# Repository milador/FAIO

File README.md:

# FAIO - Feather All-in-One Switch Wings

FAIO assistive technology wings are assistive technology wings developed to provide a modular solution for those with high level of physical disabilities to interact with touch screen devices and personal computers.

## FAIO 1.0

Faio 1.0 is no longer under development and deprecated in favor of new FAIO 2.0 feather assistive technology wings.

## FAIO 2.0

Faio 2.0 is available in two different versions:

1. <a href="https://github.com/milador/FAIO-Multiplexer">FAIO-Multiplexer</a>
2. <a href="https://github.com/milador/FAIO-Sip-And-Puff">FAIO-Sip-And-Puff</a>

## License 

### MIT License

Copyright (c) 2017 Milador

Permission is hereby granted, free of charge, to any person obtaining a copy of this software and associated documentation files (the "Software"), to deal in the Software without restriction, including without limitation the rights to use, copy, modify, merge, publish, distribute, sublicense, and/or sell copies of the Software, and to permit persons to whom the Software is furnished to do so, subject to the following conditions:

The above copyright notice and this permission notice shall be included in all copies or substantial portions of the Software.

THE SOFTWARE IS PROVIDED "AS IS", WITHOUT WARRANTY OF ANY KIND, EXPRESS OR IMPLIED, INCLUDING BUT NOT LIMITED TO THE WARRANTIES OF MERCHANTABILITY, FITNESS FOR A PARTICULAR PURPOSE AND NONINFRINGEMENT. IN NO EVENT SHALL THE AUTHORS OR COPYRIGHT HOLDERS BE LIABLE FOR ANY CLAIM, DAMAGES OR OTHER LIABILITY, WHETHER IN AN ACTION OF CONTRACT, TORT OR OTHERWISE, ARISING FROM, OUT OF OR IN CONNECTION WITH THE SOFTWARE OR THE USE OR OTHER DEALINGS IN THE SOFTWARE.

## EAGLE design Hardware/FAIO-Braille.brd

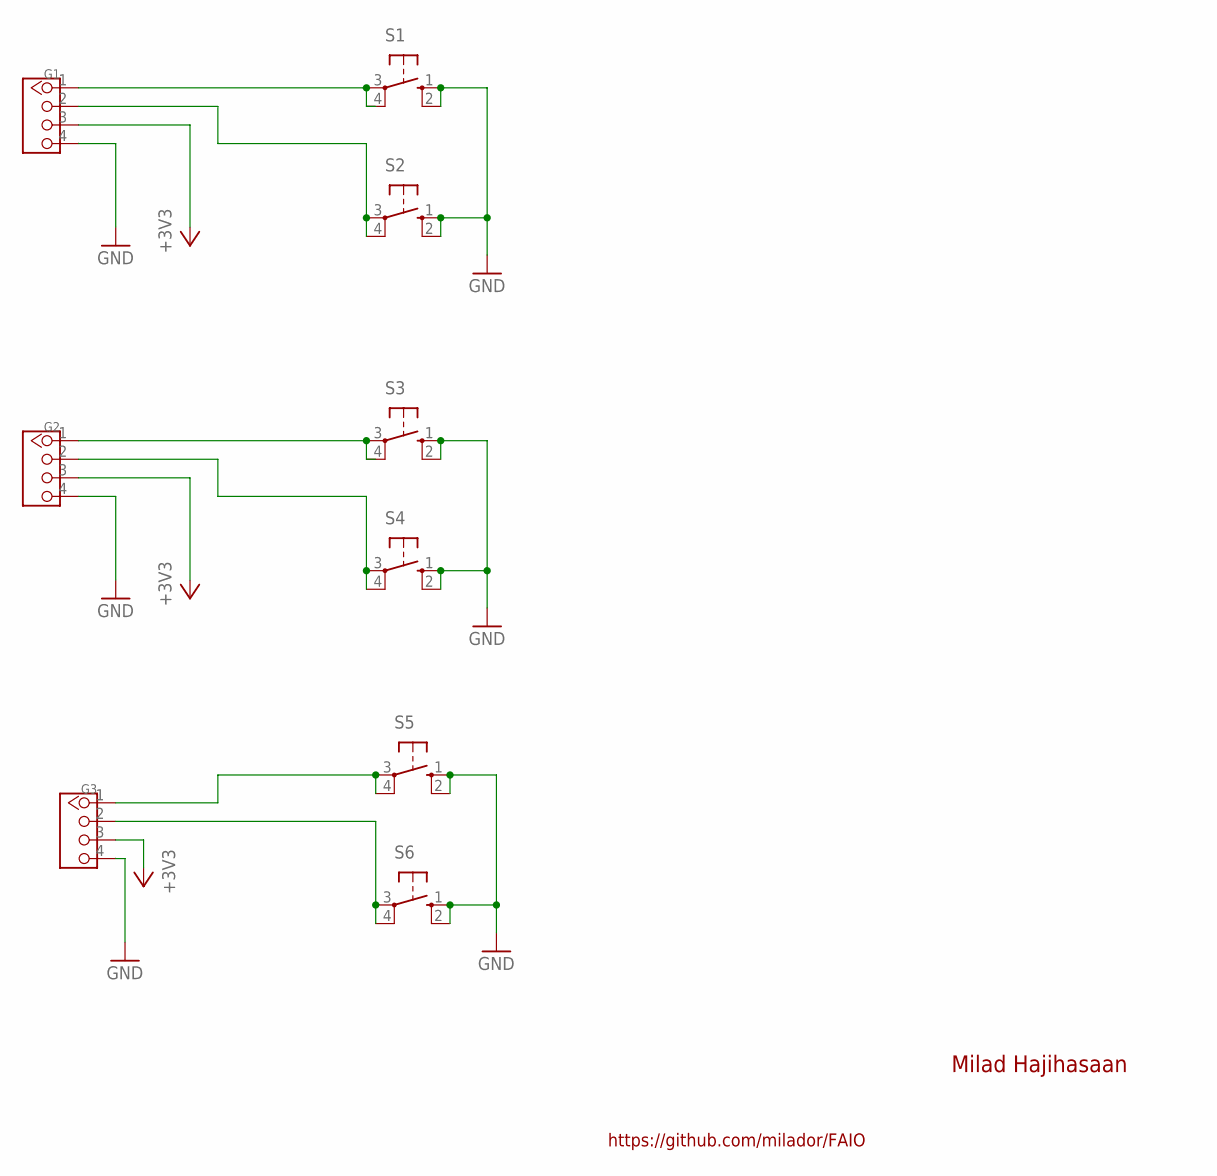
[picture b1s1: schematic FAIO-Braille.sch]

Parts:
G1, G2, G3: TWIG-4P-2.0'90D'; 4P-2.0-90D
S1, S2, S3, S4, S5, S6: 10-XX; B3F-10XX

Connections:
+3V3: G1.3, G2.3, G3.3
GND: G1.4, G2.4, G3.4, S1.1 (S), S1.2 (S1), S2.1 (S), S2.2 (S1), S3.1 (S), S3.2 (S1), S4.1 (S), S4.2 (S1), S5.1 (S), S5.2 (S1), S6.1 (S), S6.2 (S1)
unnamed: G1.1, S1.3, S1.4 (P1)
unnamed: G1.2, S2.3, S2.4 (P1)
unnamed: G2.1, S3.3, S3.4 (P1)
unnamed: G2.2, S4.3, S4.4 (P1)
unnamed: G3.2, S6.3, S6.4 (P1)
unnamed: G3.1, S5.3, S5.4 (P1)

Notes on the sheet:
Milad Hajihasaan
https://github.com/milador/FAIO

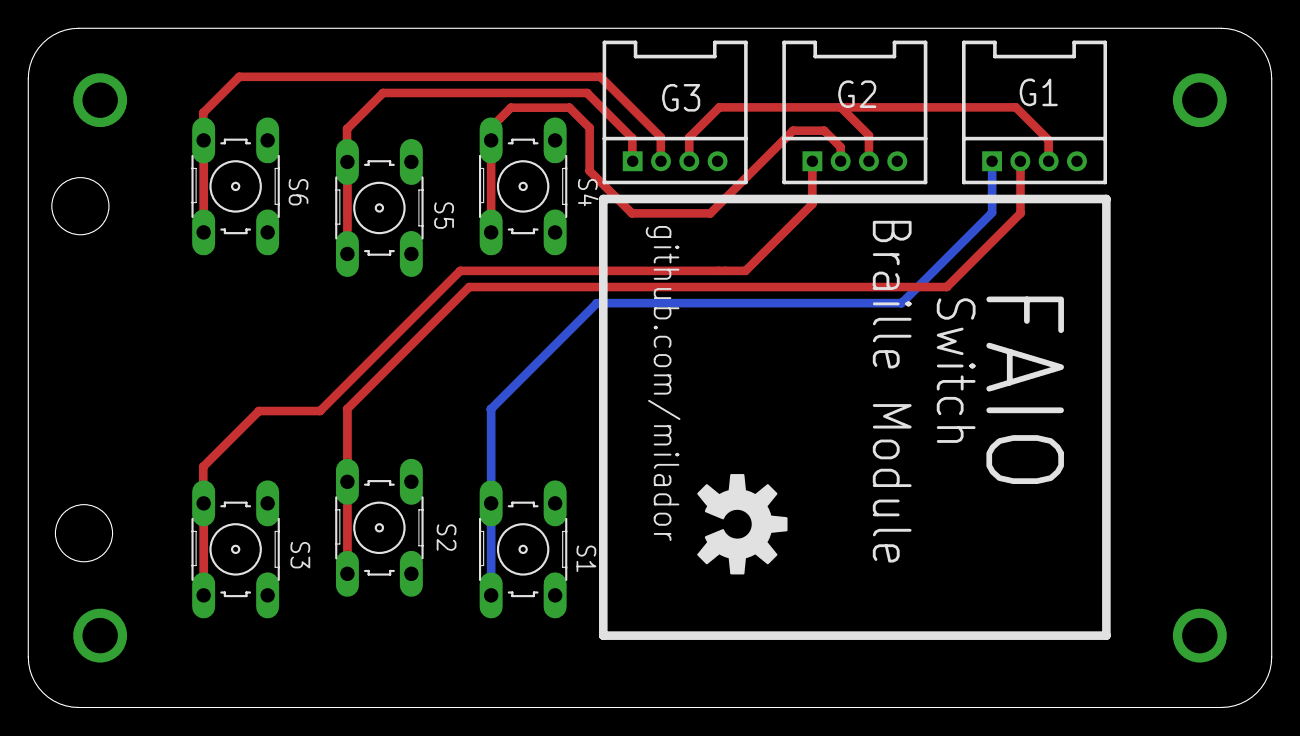
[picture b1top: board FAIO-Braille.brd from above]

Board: 2 copper layers, 87.9 x 48.0 mm, 10 parts (0 on the bottom side), 8 nets.

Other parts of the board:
U$1: OSHW-LOGO-L

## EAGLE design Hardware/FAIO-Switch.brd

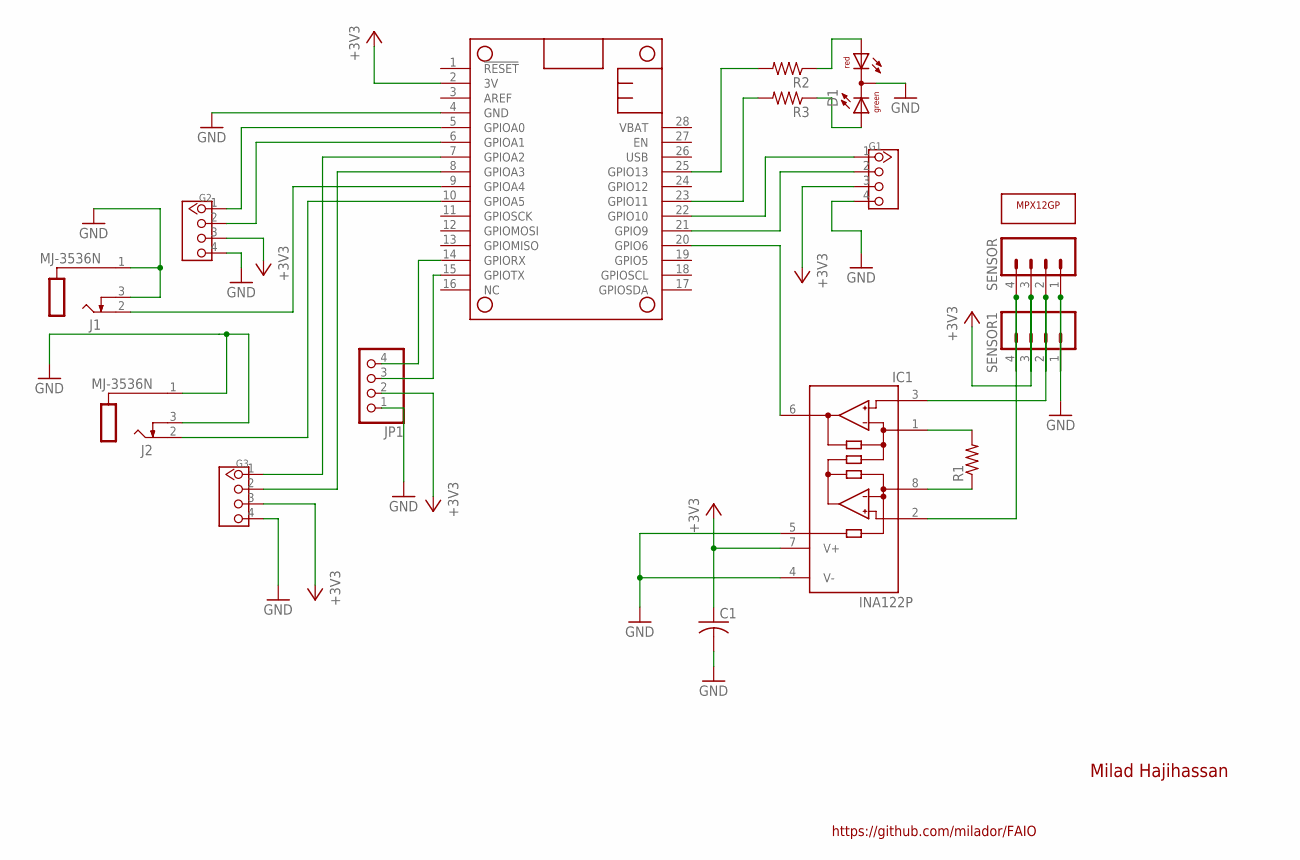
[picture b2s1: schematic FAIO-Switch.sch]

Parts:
C1: C-US025-024X044; C025-024X044
D1: DUOLED5MM
G1, G2, G3: TWIG-4P-2.0'90D'; 4P-2.0-90D
IC1: INA122P; DIL08
J1, J2: MJ-3536N
JP1: PINHD-1X4; 1X04
MS1: FEATHERWING_NODIM; FEATHERWING_DIM
R1, R2, R3: R-US_0204/7; 0204/7
SENSOR, SENSOR1: M04PTH; 1X04
U1: MPX12GP

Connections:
+3V3: C1.1, G1.3, G2.3, G3.3, IC1.7 (V+), JP1.2, MS1.2 (3V), SENSOR.3, SENSOR1.3
GND: C1.2, D1.K (C), G1.4, G2.4, G3.4, IC1.4 (V-), IC1.5 (REF), J1.1 (S), J1.3 (TS), J2.1 (S), J2.3 (TS), JP1.1, MS1.4 (GND), SENSOR.1, SENSOR1.1
unnamed: IC1.3 (+IN), SENSOR.2, SENSOR1.2
unnamed: IC1.2 (-IN), SENSOR.4, SENSOR1.4
unnamed: IC1.1 (RG), R1.2
unnamed: IC1.8 (RG), R1.1
unnamed: MS1.25 (GPIO13), R2.2
unnamed: D1.AR, R2.1
unnamed: D1.AG, R3.1
unnamed: MS1.23 (GPIO11), R3.2
unnamed: IC1.6 (OUT), MS1.20 (GPIO6)
unnamed: JP1.3, MS1.15 (GPIOTX)
unnamed: J1.2 (T), MS1.9 (GPIOA4)
unnamed: JP1.4, MS1.14 (GPIORX)
unnamed: G3.1, MS1.7 (GPIOA2)
unnamed: G1.1, MS1.22 (GPIO10)
unnamed: J2.2 (T), MS1.10 (GPIOA5)
unnamed: G2.2, MS1.6 (GPIOA1)
unnamed: G2.1, MS1.5 (GPIOA0)
unnamed: G1.2, MS1.21 (GPIO9)
unnamed: G3.2, MS1.8 (GPIOA3)

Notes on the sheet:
https://github.com/milador/FAIO
Milad Hajihassan

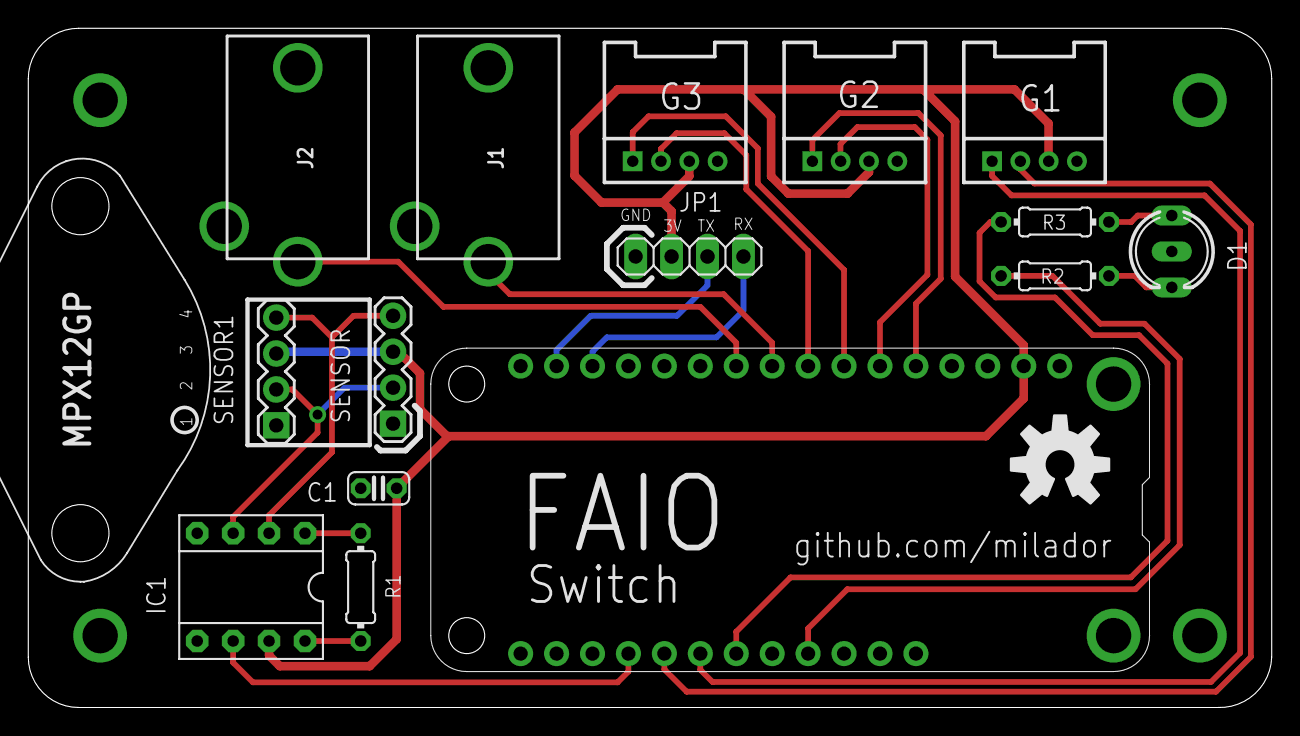
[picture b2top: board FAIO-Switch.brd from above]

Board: 2 copper layers, 87.9 x 48.0 mm, 17 parts (0 on the bottom side), 21 nets.

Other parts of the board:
U$1: OSHW-LOGO-L

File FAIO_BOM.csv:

Index,Version ,Quantity,Part Number,Manufacturer Part Number,Description,Customer Reference,Backorder,Unit Price (CAD),Total Price (CAD)
1,All,1,1597-1083-ND,110990037,GROVE 2MM 4PIN R/A CONN 10PACK,,0,2.05,
2,All,1,INA122PA-ND,INA122PA,IC OPAMP INSTR 120KHZ 8DIP,,0,8.63,
3,All,1,S5479-ND,PPPC041LGBN-RC,"CONN FEMALE 4POS .100"" R/A GOLD",,0,1.02,
4,All,2,CP-3536N-ND,MJ-3536N,CONN JACK MONO 3.5MM R/A,,0,0.94,
5,All,1,S7045-ND,PPPC121LFBN-RC,"CONN HEADER FMALE 12POS .1"" GOLD",,0,1.36,
6,All,1,S7049-ND,PPPC161LFBN-RC,"CONN HEADER FMALE 16POS .1"" GOLD",,0,1.7,
7,All,1,2.4KQBK-ND,CFR-25JB-52-2K4,RES 2.4K OHM 1/4W 5% AXIAL,,0,0.09,
8,All,1,67-1327-ND,SSL-LX3059IGW,LED GRN/RED DIFF 3MM ROUND T/H,,0,0.8,
9,All,2,CF14JT300RCT-ND,CF14JT300R,RES 300 OHM 1/4W 5% AXIAL,,0,0.06,
10,All,1,BC1160CT-ND,K104Z15Y5VF5TL2,CAP CER 0.1UF 50V Y5V RADIAL,,0,0.179,
11,All,1,  1528-1517-ND ,2829,ADAFRUIT FEATHER 32U4 BLUEFRUIT ,,0,40.2,
12,All ,1,1568-1493-ND ,PRT-13851,BATTERY LITHIUM 3.7V 400MAH ,,0,6.17,64.199
13,Sip-and-Puff,1,MPX12GP-ND,MPX12GP,SENSOR GAUGE PRESS 1.45PSI MAX,,0,14.33,78.529
14,Braille & Developer,1,1597-1089-ND,110990027,GROVE 4PIN CABLES 5PACK 20CM,,0,3.97,
15,Braille,6,679-2428-ND,MJTP1230,SWITCH TACTILE SPST-NO 0.05A 12V,,0,0.16,
16,Braille,4,AE10862-ND ,V6516H ,HEX STANDOFF M2.5 BRASS 25MM ,,0,0.59,
17,Braille,8,36-29301-ND ,29301,MACHINE SCREW PAN SLOTTED M2.5 ,,0,0.58,
,,,,,,,,Subtotal,90.459

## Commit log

2017-08-31 Added the part list
2017-09-30 Updated Components list
2017-09-30 Added PCB files
2017-09-30 Added Lithium Ion Polymer Battery to components list
2017-09-30 FAIO Instructions Manual was added
2017-10-06 Updated BOM and board layouts
2017-10-08 Updated Part list
2017-10-12 Firmware is added.
2017-10-12 Updated the manual.
2017-10-22 Readme added
2017-10-30 no message
2017-11-02 Updated firmware
2017-12-02 Fixed switch delay.
2018-04-28 Added housing STL Files
2021-02-26 Create LICENSE

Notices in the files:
parts and their libraries:
SparkFun-Aesthetics: Licensing: Creative Commons ShareAlike 4.0 International - https://creativecommons.org/licenses/by-sa/4.0
SparkFun-Connectors: Licensing: CC v3.0 Share-Alike You are welcome to use this library for commercial purposes.
con-cuistack: Copyright (C) 2008, Bob Starr
